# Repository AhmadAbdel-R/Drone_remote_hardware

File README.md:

# Drone Remote Hardware

Hardware workspace for my capstone remote + FCU board iterations.

## Repo Layout

- `hardware/fcu/FCU-hardware/`
  - FCU KiCad project and production artifacts
- `hardware/remote/FC_Remote-hardware/`
  - remote controller KiCad project and production artifacts
- `hardware/remote/FC_Remote-hardware/nrf_breakout/`
  - nRF breakout board subproject
- `mechanical/enclosure/`
  - enclosure and mechanical exports
- `mechanical/enclosure/remote_enclosure_stl/`
  - upload area for new remote enclosure STL revisions
- `mechanical/fcu/top_plate_updated_frame/`
  - upload area for updated FCU top plate/frame files
- `docs/`
  - repo organization notes

## Tools

- KiCad for schematic + PCB
- STEP/STL/3MF for mechanical handoff

## Practical Note

A lot of old backups and generated production files are intentionally kept for traceability between board revisions.

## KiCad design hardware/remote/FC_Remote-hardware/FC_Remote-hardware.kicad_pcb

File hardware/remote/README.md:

# Remote Hardware

This folder contains the primary remote controller PCB project.

Main KiCad project path:

- `FC_Remote-hardware.kicad_pro`

Also includes:

- manufacturing outputs
- historical backups
- support subprojects (including nRF breakout)

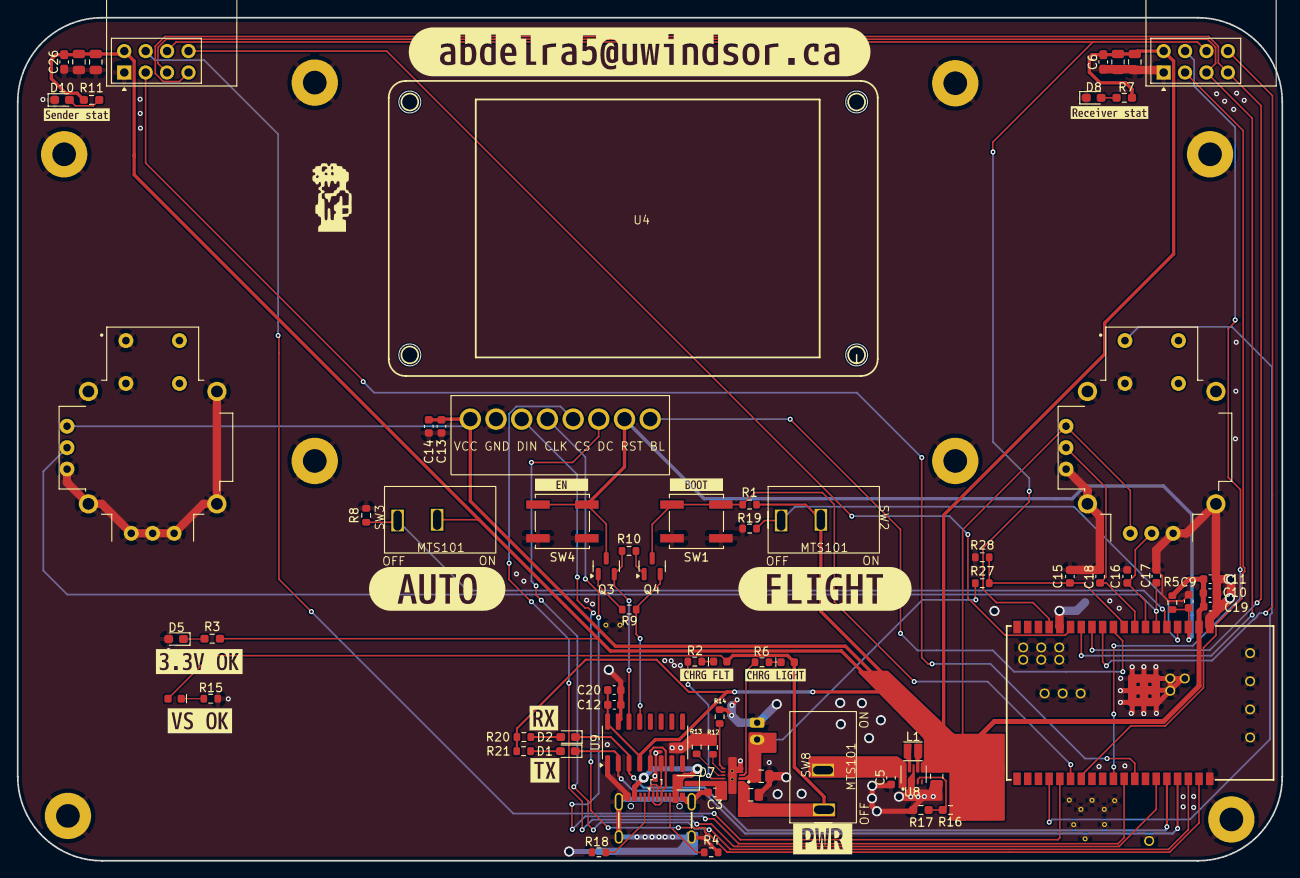
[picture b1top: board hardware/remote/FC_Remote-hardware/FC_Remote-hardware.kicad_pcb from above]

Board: 4 copper layers, 150.0 x 100.0 mm, 89 parts (1 on the bottom side), 56 nets.

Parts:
BT1: Battery_Cell; JST_PH_B2B-PH-K_1x02_P2.00mm_Vertical
C1, C2, C4, C7, C8, C21, C22: 22uF; C_0805_2012Metric
C3, C9, C10, C12, C13: 1uF; C_0603_1608Metric
C5, C11: 10uF; C_0603_1608Metric
C6, C26: 0.1uF; C_0603_1608Metric_Pad1.08x0.95mm_HandSolder
C14, C15, C16, C17, C18, C19, C20: 0.1uF; C_0603_1608Metric
D1, D2, D5: LED; LED_0603_1608Metric_Pad1.05x0.95mm_HandSolder
D3: Green; LED_0603_1608Metric_Green
D4: Yellow; LED_0603_1608Metric_Yellow
D6: Red; LED_0603_1608Metric_Red
D7: PMEG4020EJ; D_SOD-323
D8, D10: GREEN; LED_0603_1608Metric_Pad1.05x0.95mm_HandSolder
J1: USB_C_Receptacle; USB-C_16
L1: 0.47 uH; L_Changjiang_FTC201608S
Q3, Q4: MMBT2222A; SOT-23
R1, R5: 10k; R_0603_1608Metric
R2, R6: 5K; R_0603_1608Metric
R3, R7, R11: 5K; R_0603_1608Metric_Pad0.98x0.95mm_HandSolder
R4, R18: 5.1k; R_0603_1608Metric
R8, R9, R10, R14, R19, R27, R28: 10K; R_0603_1608Metric
R12: 13K; R_0603_1608Metric
R13: 600; R_0603_1608Metric
R15: 1K; R_0603_1608Metric
R16: 511K; R_0603_1608Metric_Pad0.98x0.95mm_HandSolder
R17: 91K; R_0603_1608Metric_Pad0.98x0.95mm_HandSolder
R20, R21: 470; R_0603_1608Metric
SW1, SW4: SW_Push; SW_Push_1P1T_NO_CK_KSC7xxJ
SW2, SW3, SW8: SW_SPST; mts101sw
U1, U2: COM-09032; XDCR_COM-09032
U3: BQ25185DLHR; IC_BQ25185DLHR
U4: ST7789_2IN_WS; Waveshare_2inch_foot
U5: ESP32-WROVER-E-N16R8; ESP32-WROVER-E-IE
U6: TPD2EUSB30; Texas_DRT-3
U7, U12: NRF24L01_Breakout; nRF24L01_Breakout
U8: TPS63802DLAR; VREG_TPS63802DLAR
U9: CH340C; SOIC-16_3.9x9.9mm_P1.27mm
kibuzzard-69B816EF: G***; kibuzzard-69B816EF
kibuzzard-69B818B8: G***; kibuzzard-69B818B8
kibuzzard-69B818DE: G***; kibuzzard-69B818DE
kibuzzard-69B825AF: G***; kibuzzard-69B825AF
kibuzzard-69B825F7: G***; kibuzzard-69B825F7
kibuzzard-69B842D9: G***; kibuzzard-69B842D9
kibuzzard-69B842E6: G***; kibuzzard-69B842E6
kibuzzard-69B8345C: G***; kibuzzard-69B8345C
kibuzzard-69B8399F: G***; kibuzzard-69B8399F
kibuzzard-69B81705: G***; kibuzzard-69B81705
kibuzzard-69B83530: G***; kibuzzard-69B83530
kibuzzard-69B84485: G***; kibuzzard-69B84485
kibuzzard-69B84493: G***; kibuzzard-69B84493
kibuzzard-6967276B: G***; kibuzzard-6967276B

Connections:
0_ESP: Q4.3 (C), R1.1, SW1.1, U5.25 (IOA0)
+3.3V: C1.1, C6.1, C7.1, C8.1, C10.1, C11.2, C12.2, C13.1, C14.1, C19.2, C20.2, C21.1, C22.1, C26.1, R1.2, R3.2, R5.1, R7.1, R11.1, R16.1, R20.1, R21.1, SW2.2 (B), SW3.2 (B), U1.V1 (V+), U2.H1 (H+), U2.V1 (V+), U4.1 (VCC), U5.2 (VDD), U7.2 (VCC), U8.6 (VOUT), U9.4 (V3), U9.16 (VCC), U12.2 (VCC)
+5V: C3.1, D7.1 (K), U3.10 (IN)
AUTONOMY_SW: R8.1, SW3.1 (A), U5.5 (IA39)
BATT_ADC: C15.1, R27.2, R28.2, U5.9 (IOA33)
CHIP_PU: C9.1, Q3.3 (C), R5.2, SW4.1, U4.7 (RST), U5.3 (EN)
CTRL_CE: U5.31 (IO19), U12.3 (CE)
CTRL_CSN: U5.24 (IOA2), U12.4 (~CSN)
CTRL_IRQ: U5.14 (IOA12), U12.8 (IRQ)
DIR_JOY_BTN: U2.B1A (SEL+), U5.23 (IOA15)
DIR_JOY_X: C16.1, U2.H2 (H), U5.7 (IA35)
DIR_JOY_Y: C18.1, U2.V2 (V), U5.8 (IOA32)
DTR: Q4.2 (E), R9.2, U9.13 (~DTR)
FLIGHT_MODE_SW: R19.1, SW2.1 (A), U5.4 (IA36)
GND: BT1.1 (+), C1.2, C2.2, C3.2, C4.2, C5.2, C6.2, C7.2, C8.2, C9.2, C10.2, C11.1, C12.1, C13.2, C14.2, C15.2, C16.2, C17.2, C18.2, C19.1, C20.1, C21.2, C22.2, C26.2, D5.2 (A), D8.1 (K), D10.1 (K), J1.GND, J1.NC1, J1.NC2, J1.NC3, J1.S (NC), R4.2, R8.2, R12.1, R13.1, R14.2, R15.1, R17.2, R18.2, R19.2, R28.1, SW1.2, SW4.2, U1.B1A (SEL+), U1.B2A (SEL-), U1.H1 (H+), U1.H2 (H), U1.H3 (H-), U1.S1 (SHIELD), U1.S2 (SHIELD), U1.S3 (SHIELD), U1.S4 (SHIELD), U1.V3 (V-), U2.B2A (SEL-), U2.H3 (H-), U2.S1 (SHIELD), U2.S2 (SHIELD), U2.S3 (SHIELD), U2.S4 (SHIELD), U2.V3 (V-), U3.4 (~CE), U3.5 (GND), U3.11 (THERMAL_PAD), U3.12, U3.13, U4.2 (GND), U5.1 (GND), U5.15 (GND), U5.38 (GND), U5.39.1 (GND), U5.39.2 (GND), U5.39.3 (GND), U5.39.4 (GND), U5.39.5 (GND), U5.39.6 (GND), U5.39.7 (GND), U5.39.8 (GND), U5.39.9 (GND), U6.3 (GND), U7.1 (GND), U8.2 (MODE), U8.3 (AGND), U8.8 (GND), U9.1 (GND), U9.15 (R232), U12.1 (GND)
NRF_MISO: U5.12 (IOA27), U7.7 (MISO), U12.7 (MISO)
NRF_MOSI: U5.16 (IOA13), U7.6 (MOSI), U12.6 (MOSI)
NRF_SCK: U5.13 (IOA14), U7.5 (SCK), U12.5 (SCK)
unnamed: D1.2 (A), R21.2
unnamed: D2.2 (A), R20.2
unnamed: D3.1 (K), R15.2
unnamed: D4.1 (K), R6.1
unnamed: D5.1 (K), R3.1
unnamed: D6.1 (K), R2.1
unnamed: D7.2 (A), J1.VBUS
unnamed: D8.2 (A), R7.2
unnamed: D10.2 (A), R11.2
unnamed: J1.A5 (CC1), R18.1
unnamed: J1.B5 (CC2), R4.1
unnamed: Q3.1 (B), R9.1
unnamed: Q4.1 (B), R10.2
unnamed: R12.2, U3.7 (ILIM/VSET)
unnamed: R13.2, U3.8 (ISET)
unnamed: R2.2, U3.9 (STAT1)
unnamed: R6.2, U3.3 (STAT2)
unnamed: R14.1, U3.6 (TS/MR)
unnamed: R16.2, R17.1, U8.4 (FB)
unnamed: L1.2, U8.9 (L1)
unnamed: L1.1, U8.7 (L2)
RTS: Q3.2 (E), R10.1, U9.14 (~RTS)
RX_ESP: D2.1 (K), U5.34 (RXD0/IO3), U9.3 (RXD)
TELM_CE: U5.26 (IOA4), U7.3 (CE)
TELM_CSN: U5.29 (IO5), U7.4 (~CSN)
TELM_IRQ: U5.11 (IOA26), U7.8 (IRQ)
TFT_BL: U4.8 (BL), U5.10 (IOA25)
TFT_CS: U4.5 (CS), U5.33 (IO21)
TFT_DC: U4.6 (DC), U5.36 (IO22)
TFT_MOSI: U4.3 (DIN), U5.37 (IO23)
TFT_SCK: U4.4 (SCLK), U5.30 (IO18)
THROTTLE_JOY: C17.1, U1.V2 (V), U5.6 (IA34)
TX_ESP: D1.1 (K), U5.35 (TXD0/IO1), U9.2 (TXD)
USB_D+_ESP: J1.A6 (D+), J1.B6 (D+), U6.1 (D+), U9.5 (UD+)
USB__D-_ESP: J1.A7 (D-), J1.B7 (D-), U6.2 (D-), U9.6 (UD-)
VBAT: BT1.2 (-), C4.1, R27.1, U3.2 (BAT)
VIN_3.3: C5.1, SW8.2 (B), U8.1 (EN), U8.10 (VIN)
VS: C2.1, D3.2 (A), D4.2 (A), D6.2 (A), SW8.1 (A), U3.1 (SYS)

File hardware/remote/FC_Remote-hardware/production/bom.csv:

Designator,Footprint,Quantity,Value,LCSC Part #
BT1,JST_PH_B2B-PH-K_1x02_P2.00mm_Vertical,1,Battery_Cell,
"C1, C2, C21, C22, C4, C7, C8",0805,7,22uF,
"C10, C12, C13, C3, C9",0603,5,1uF,
"C11, C5",0603,2,10uF,
"C14, C15, C16, C17, C18, C19, C20, C26, C6",0603,9,0.1uF,
"D1, D2, D5",0603,3,LED,
"D10, D3, D8",0603,3,GREEN,
D4,0603,1,Yellow,
D6,0603,1,Red,
D7,D_SOD-323,1,PMEG4020EJ,
J1,USB-C_16,1,USB_C_Receptacle,
L1,L_Changjiang_FTC201608S,1,0.47 uH,
"Q3, Q4",SOT-23,2,MMBT2222A,
"R1, R10, R14, R19, R27, R28, R5, R8, R9",0603,9,10k,
"R11, R2, R3, R6, R7",0603,5,5K,
R12,0603,1,13K,
R13,0603,1,600,
R15,0603,1,1K,
R16,0603,1,511K,
R17,0603,1,91K,
"R18, R4",0603,2,5.1k,
"R20, R21",0603,2,470,
"SW1, SW4",SW_Push_1P1T_NO_CK_KSC7xxJ,2,SW_Push,
"SW2, SW3, SW8",mts101sw,3,SW_SPST,
"U1, U2",XDCR_COM-09032,2,COM-09032,
"U12, U7",nRF24L01_Breakout,2,NRF24L01_Breakout,
U3,IC_BQ25185DLHR,1,BQ25185DLHR,
U4,Waveshare_2inch_foot,1,ST7789_2IN_WS,
U5,ESP32-WROVER-E-IE,1,ESP32-WROVER-E-N16R8,
U6,Texas_DRT-3,1,TPD2EUSB30,
U8,VREG_TPS63802DLAR,1,TPS63802DLAR,
U9,SOIC-16_3.9x9.9mm_P1.27mm,1,CH340C,

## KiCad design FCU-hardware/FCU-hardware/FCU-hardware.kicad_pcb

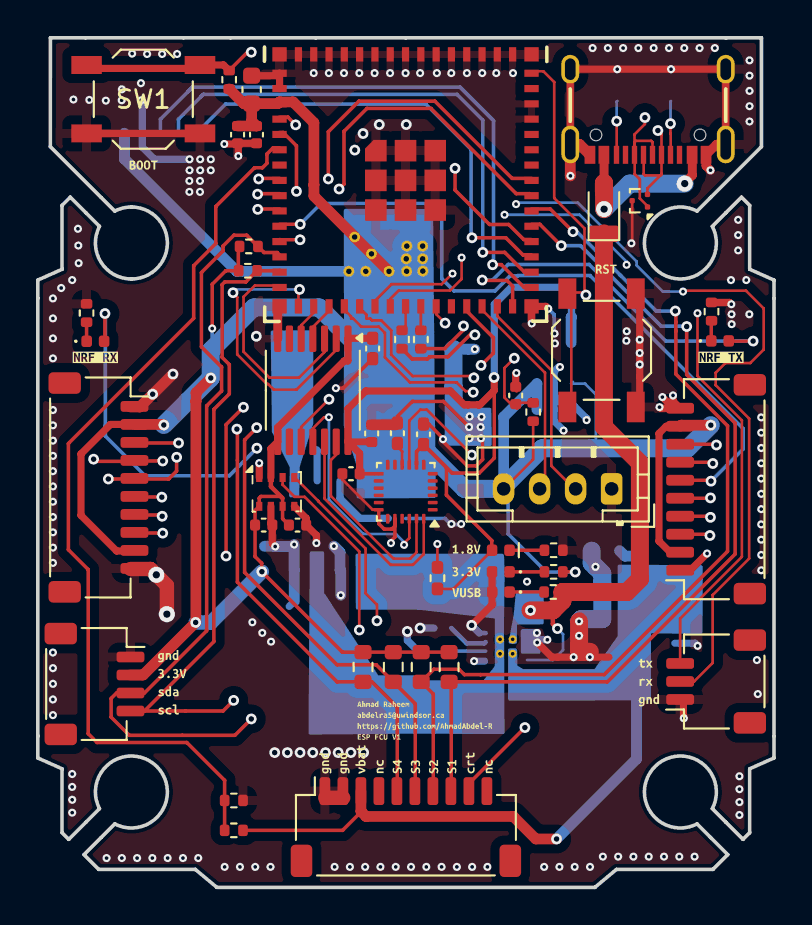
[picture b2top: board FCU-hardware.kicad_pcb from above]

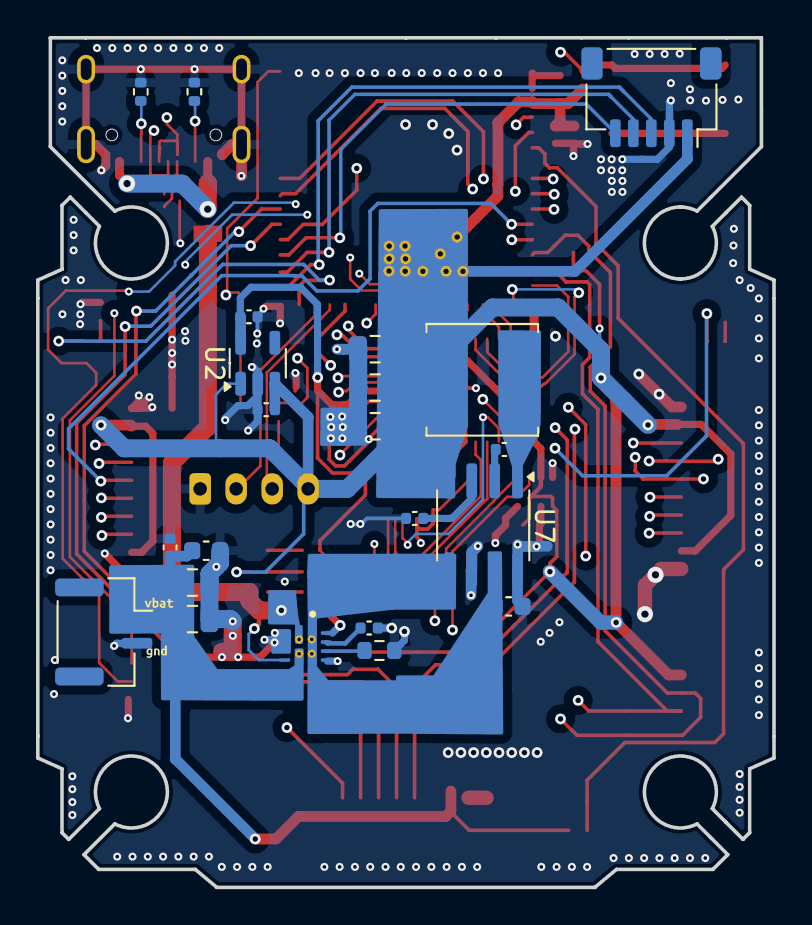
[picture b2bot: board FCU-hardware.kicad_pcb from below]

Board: 4 copper layers, 40.9 x 47.2 mm, 84 parts (24 on the bottom side), 60 nets.

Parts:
C1, C13, C15, C17, C19, C20, C23: 0.1uF; C_0402_1005Metric
C2, C3, C9, C10, C16, C18: 1uF; C_0402_1005Metric
C4, C12, C14: 0.1uF; C_0402_1005Metric_Pad0.74x0.62mm_HandSolder
C5, C6, C7, C21, C22: 22uF; C_0805_2012Metric
C8, C11: 10uF; C_0603_1608Metric
C24: 1uF; C_0603_1608Metric
D1: Red; LED_0402_1005Metric_Red
D2: Blue; LED_0402_1005Metric
D3, D4: Green; LED_0402_1005Metric
D5: LED; LED_0402_1005Metric
D7: PMEG4020EJ; D_SOD-323
J1: USB_C_Receptacle; USB-C_16(CUSTOM)
J2: Conn_01x04; JST_SH_SM04B-SRSS-TB_1x04-1MP_P1.00mm_Horizontal
J4: Conn_01x04; JST_PH_B4B-PH-K_1x04_P2.00mm_Vertical
J5: Conn_01x03; JST_SH_SM03B-SRSS-TB_1x03-1MP_P1.00mm_Horizontal
J7, J8, J15: Conn_01x10; JST_SH_SM10B-SRSS-TB_1x10-1MP_P1.00mm_Horizontal
J9: Conn_01x02; JST_GH_SM02B-GHS-TB_1x02-1MP_P1.25mm_Horizontal
J14: Conn_01x05; JST_SH_SM05B-SRSS-TB_1x05-1MP_P1.00mm_Horizontal
L1: 22 uH; L_Bourns_SRN6045TA
R1, R2: 22; R_0402_1005Metric
R3: 1.5K; R_0402_1005Metric
R4, R18: 5.1k; R_0402_1005Metric
R5, R6: 10k; R_0402_1005Metric
R7: 59K; R_0603_1608Metric
R8: 500; R_0402_1005Metric
R9, R10: 4.7K; R_0402_1005Metric
R11: 3K; R_0402_1005Metric
R12, R13: 1K; R_0402_1005Metric
R14: 22K; R_0402_1005Metric
R15: 100K; R_0402_1005Metric
R19: 100K; R_0402_1005Metric_Pad0.72x0.64mm_HandSolder
R28, R29, R30, R31: DNP; R_0603_1608Metric
SW1, SW4: SW_Push; SW_SPST_TL3342
U1: ESP32-S3-MINI; ESP32-MINI
U2: MIC5504-1.8YM5-TR; SOT-23-5
U3: ICM-20948; InvenSense_QFN-24_3x3mm_P0.4mm
U4: TXU0304PWR; TSSOP-14_4.4x5mm_P0.65mm
U5: BMP280; Bosch_LGA-8_2x2.5mm_P0.65mm_ClockwisePinNumbering
U6: TPD2EUSB30; Texas_DRT-3
U7: L6982N33DR; SOIC-8_3.9x4.9mm_P1.27mm
U8: TPS2121RUXR; IC_TPS2121RUXR
kibuzzard-69CA970F: G***; kibuzzard-69CA970F
kibuzzard-69CA973C: G***; kibuzzard-69CA973C
kibuzzard-69CA975F: G***; kibuzzard-69CA975F
kibuzzard-69CA983A: G***; kibuzzard-69CA983A
kibuzzard-69CA985D: G***; kibuzzard-69CA985D
kibuzzard-69CA986D: G***; kibuzzard-69CA986D
kibuzzard-69CA9883: G***; kibuzzard-69CA9883
kibuzzard-69CAA37E: G***; kibuzzard-69CAA37E
kibuzzard-69CAA38B: G***; kibuzzard-69CAA38B
kibuzzard-69CAA374: G***; kibuzzard-69CAA374
kibuzzard-69CD68AD: G***; kibuzzard-69CD68AD
kibuzzard-69CD68C1: G***; kibuzzard-69CD68C1
kibuzzard-69CDB16D: G***; kibuzzard-69CDB16D

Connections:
0_ESP: R6.1, SW1.1, U1.4 (IO0)
1.8V: C3.2, C12.2, C13.1, C15.2, D1.2 (A), R19.2, U2.5 (VOUT), U3.8 (VDDIO), U3.13 (VDD), U4.14 (VCCB)
+3.3V: C2.2, C5.1, C10.1, C11.2, C14.1, C16.2, C17.1, C19.2, C21.1, C22.1, J2.2, J4.4, J7.2, J7.9, J14.1, J15.2, J15.9, L1.2, R3.2, R5.1, R6.2, R9.1, R10.1, R28.1, R29.1, R30.1, R31.1, U1.3 (3V3), U2.1 (VIN), U2.3 (EN), U4.1 (VCCA), U4.8 (OE), U5.2 (CSB), U5.6 (VDDIO), U5.8 (VDD), U7.4 (VOUT/FB)
CHIP_PU: C9.1, R5.2, SW4.1, U1.45 (EN)
CRT: J8.9, U1.5 (IOA1)
CS/1.8: R19.1, U3.22 (~CS), U4.11 (B3Y)
CTRL_CE: J15.7, U1.19 (IOA15)
CTRL_CSN: J15.6, U1.11 (IOA7)
CTRL_IRQ: J15.8, U1.20 (IOA16)
D+: J1.A6 (D+), J1.B6 (D+), R1.2, U6.1 (D+)
D-: J1.A7 (D-), J1.B7 (D-), R2.2, U6.2 (D-)
GND: C2.1, C3.1, C4.2, C5.2, C6.2, C7.2, C8.1, C9.2, C10.2, C11.1, C12.1, C13.2, C14.2, C15.1, C16.1, C17.2, C18.2, C19.1, C20.2, C21.2, C22.2, C23.1, C24.2, D2.2 (A), D5.2 (A), J1.GND, J1.S (SHIELD), J2.1, J4.1, J5.1, J7.1, J7.10, J8.1, J8.2, J9.2, J14.2, J15.1, J15.10, R4.2, R7.2, R8.2, R12.2, R13.2, R14.2, R18.2, SW1.2, SW4.2, U1.1 (GND), U1.2 (GND), U1.42 (GND), U1.43 (GND), U1.46 (GND), U1.47 (GND), U1.48 (GND), U1.49 (GND), U1.50 (GND), U1.51 (GND), U1.52 (GND), U1.53 (GND), U1.54 (GND), U1.55 (GND), U1.56 (GND), U1.57 (GND), U1.58 (GND), U1.59 (GND), U1.60 (GND), U1.61 (GND), U1.62 (GND), U1.63 (GND), U1.64 (GND), U1.65 (GND), U2.2 (GND), U3.18 (GND), U3.20 (GND), U4.7 (GND), U5.1 (GND), U5.5 (SDO), U5.7 (GND), U6.3 (GND), U7.6 (AGND), U7.8 (PGND), U8.3 (CP2), U8.4 (OV2), U8.5 (OV1), U8.9 (ST), U8.12 (GND)
IMU_CS: U1.18 (IOA14), U4.4 (A3)
IO35: J14.3, U1.31 (IO35)
IO36: J14.4, U1.32 (IO36)
IO37: J14.5, U1.33 (IO37)
MOTOR1: J8.8, R28.2, U1.35 (IO39)
MOTOR2: J8.7, R29.2, U1.36 (IO40)
MOTOR3: J8.6, R30.2, U1.37 (IO41)
MOTOR4: J8.5, R31.2, U1.38 (IO42)
NRFRX_OK: D4.2 (A), U1.27 (IO47)
NRFTX_OK: D3.2 (A), U1.30 (IO48)
NRF_MISO: J7.5, J15.5, U1.9 (IOA5)
NRF_MOSI: J7.4, J15.4, U1.8 (IOA4)
NRF_SCK: J7.3, J15.3, U1.10 (IOA6)
unnamed: D1.1 (K), R8.1
unnamed: D2.1 (K), R11.1
unnamed: D3.1 (K), R12.1
unnamed: D4.1 (K), R13.1
unnamed: D5.1 (K), R3.1
unnamed: D7.2 (A), J1.VBUS
unnamed: J1.A5 (CC1), R18.1
unnamed: J1.B5 (CC2), R4.1
unnamed: R2.1, U1.23 (IOA19)
unnamed: R1.1, U1.24 (IOA20)
unnamed: C4.1, U3.10 (REGOUT)
unnamed: C1.1, U7.2 (BOOT)
unnamed: C1.2, L1.1, U7.1 (SW)
unnamed: C18.1, U7.3 (VCC)
unnamed: R7.1, U8.10 (ILIM)
unnamed: C23.2, U8.11 (SS)
RX_GPS: J4.2, U1.29 (IO34)
RX_RASBERRY: J5.2, U1.22 (IOA18)
SCK_IMU: U1.16 (IOA12), U4.2 (A1)
SCK/1.8V: U3.23 (SCL/SCLK), U4.13 (B1Y)
SCL: J2.4, R10.2, U1.14 (IOA10), U5.4 (SCK)
SDA: J2.3, R9.2, U1.13 (IOA9), U5.3 (SDI)
SDI_IMU: U1.15 (IOA11), U4.3 (A2)
SDI/1.8V: U3.24 (SDA/SDI), U4.12 (B2Y)
SDO_IMU: U1.17 (IOA13), U4.5 (A4Y)
SDO/1.8V: U3.9 (SDO/AD0), U4.10 (B4)
TELM_CE: J7.7, U1.25 (IO21)
TELM_CSN: J7.6, U1.12 (IOA8)
TELM_IRQ: J7.8, U1.34 (IO38)
TX_GPS: J4.3, U1.28 (IO33)
TX_RASBERRY: J5.3, U1.21 (IOA17)
VBAT: C6.1, C7.1, C20.1, C24.1, J8.3, J9.1, R15.1, U8.7 (IN1), U8.7_1 (IN1__1)
VBAT_ADC: R14.1, R15.2, U1.6 (IOA2)
VBUS: D7.1 (K), R11.2, U8.2 (IN2), U8.2_1 (IN2__1), U8.6 (PR1)
VIN_3.3: C8.2, U7.5 (EN/CLKIN), U7.7 (VIN), U8.1 (OUT), U8.1_1 (OUT__1), U8.8 (OUT__2), U8.8_1 (OUT__3)

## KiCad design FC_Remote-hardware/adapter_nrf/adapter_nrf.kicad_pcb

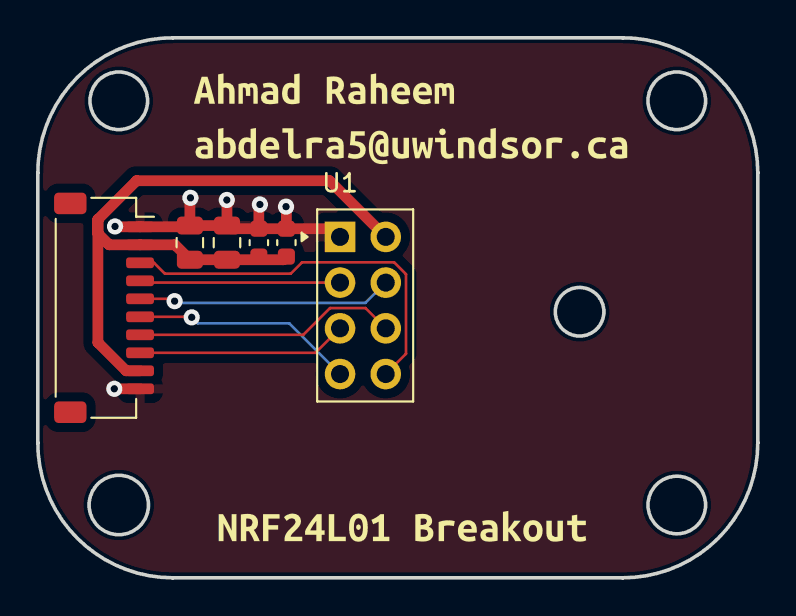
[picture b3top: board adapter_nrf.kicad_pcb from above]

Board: 4 copper layers, 40.0 x 30.0 mm, 8 parts (0 on the bottom side), 8 nets.

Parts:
C1, C2: 22uF; C_0805_2012Metric
C3: 0.1uF; C_0603_1608Metric
C4: 1.0uF; C_0603_1608Metric
J1: Conn_01x10; JST_SH_SM10B-SRSS-TB_1x10-1MP_P1.00mm_Horizontal
U1: NRF24L01_Breakout; nRF24L01_Breakout
kibuzzard-69CDF508: G***; kibuzzard-69CDF508
kibuzzard-69CDF522: G***; kibuzzard-69CDF522

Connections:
3.3V: C1.1, C2.1, C3.1, C4.1, J1.2, J1.9, U1.2 (VCC)
CE: J1.4, U1.3 (CE)
CSN: J1.5, U1.4 (~CSN)
GND: C1.2, C2.2, C3.2, C4.2, J1.1, J1.10, U1.1 (GND)
IRQ: J1.3, U1.8 (IRQ)
MISO: J1.6, U1.7 (MISO)
MOSI: J1.7, U1.6 (MOSI)
SCK: J1.8, U1.5 (SCK)

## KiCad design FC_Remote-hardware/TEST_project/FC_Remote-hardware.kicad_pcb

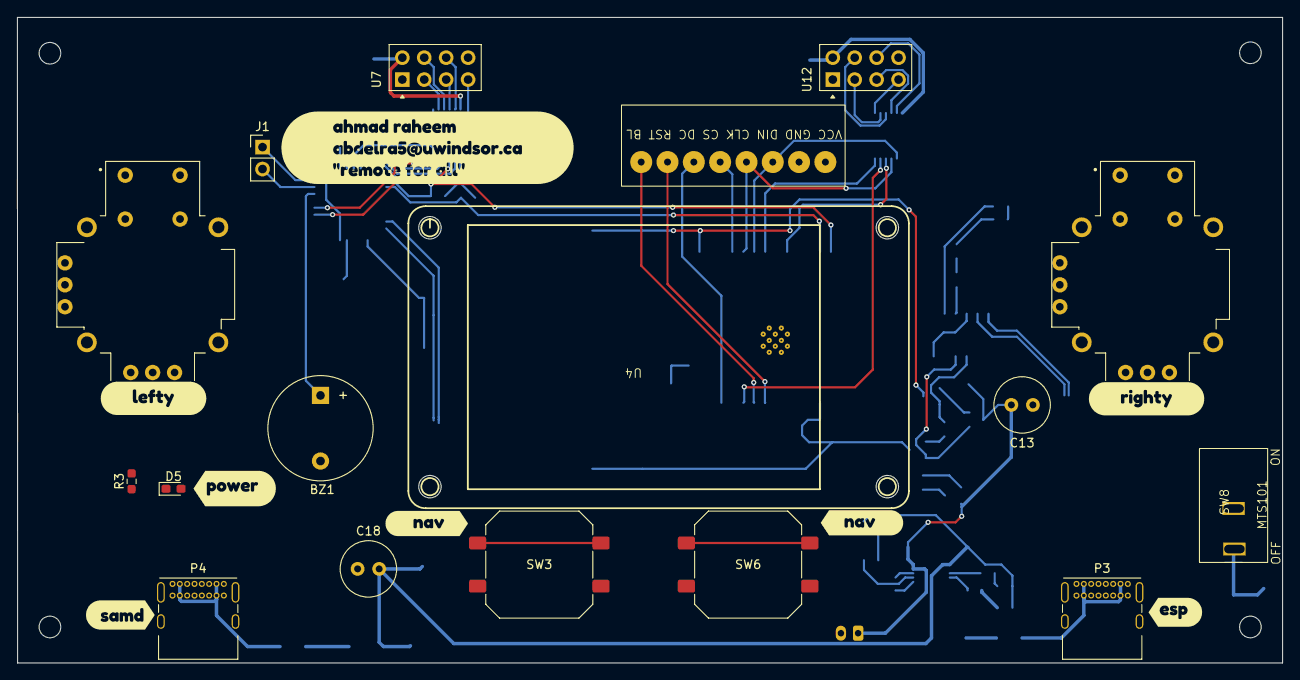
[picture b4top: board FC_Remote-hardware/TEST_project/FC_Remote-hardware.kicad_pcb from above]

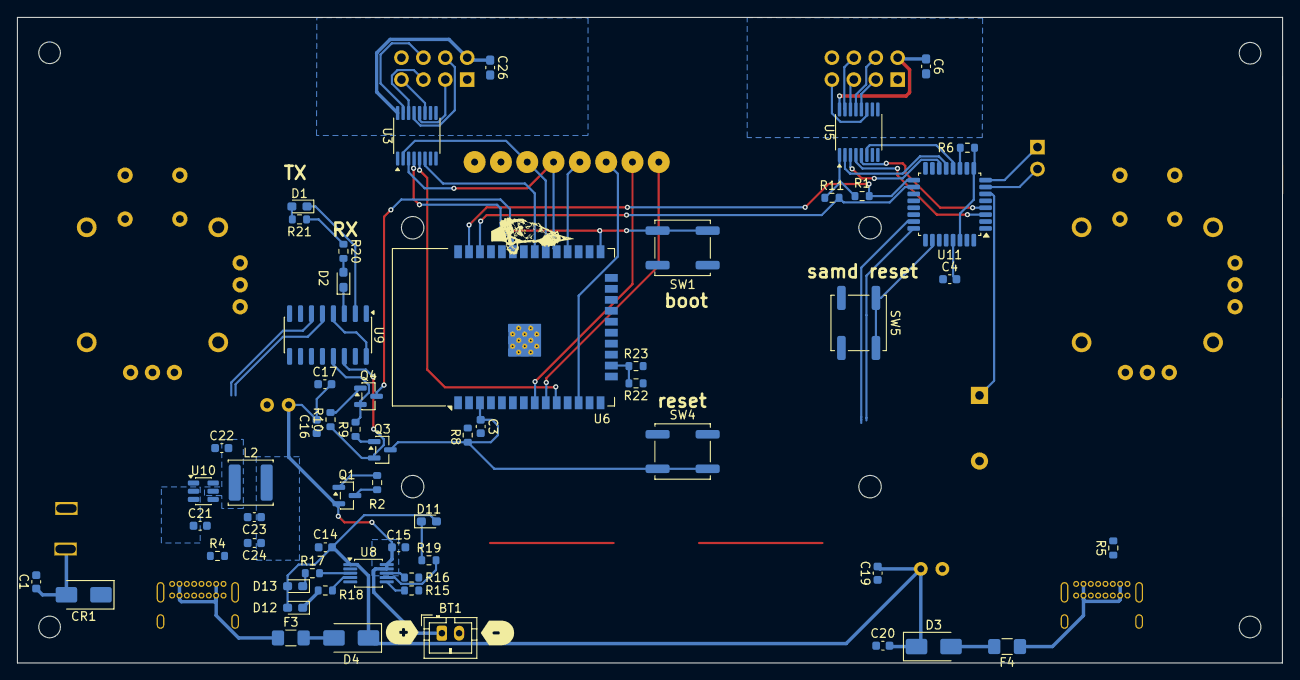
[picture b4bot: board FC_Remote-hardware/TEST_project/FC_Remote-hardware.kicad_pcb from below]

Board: 4 copper layers, 146.6 x 74.8 mm, 84 parts (60 on the bottom side), 81 nets.

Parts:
BT1: Battery_Cell; JST_PH_B2B-PH-K_1x02_P2.00mm_Vertical
BZ1: Buzzer; Buzzer_12x9.5RM7.6
C1, C16, C19, C21: 10uF; C_0603_1608Metric
C3, C4, C14, C15: 1uF; C_0603_1608Metric
C6, C26: 0.1uF; C_0603_1608Metric_Pad1.08x0.95mm_HandSolder
C13, C18: 100uF; C_Radial_D6.3mm_H5.0mm_P2.50mm
C17, C20: 0.1uF; C_0603_1608Metric
C22: 100 nF; C_0603_1608Metric
C23, C24: 22uF; C_0603_1608Metric
CR1: SSA210; D_SMA
D1, D2, D5, D11, D12, D13: LED; LED_0603_1608Metric_Pad1.05x0.95mm_HandSolder
D3, D4: SMAJ5.0A; D_SMA
F3, F4: Polyfuse; Fuse_1206_3216Metric_Pad1.42x1.75mm_HandSolder
J1: Conn_01x02_Pin; PinHeader_1x02_P2.54mm_Vertical
L2: 3.9uH; L_APV_ANR5020
P3, P4: USB_C_Plug_USB2.0; USB_C_Receptacle_GCT_USB4085
Q1: DMG3415U; SOT-23
Q3, Q4: MMBT2222A; SOT-23
R1, R11: DNP; R_0603_1608Metric
R2, R22, R23: 100K; R_0603_1608Metric
R3: 500; R_0603_1608Metric_Pad0.98x0.95mm_HandSolder
R4, R5: 5.1k; R_0603_1608Metric
R6: 5.1K; R_0603_1608Metric
R8: 10k; R_0603_1608Metric
R9, R10, R16: 10K; R_0603_1608Metric
R15: 1K; R_0603_1608Metric
R17, R18, R19: 470; R_0603_1608Metric
R20, R21: R; R_0603_1608Metric
SW1, SW4, SW5: SW_Push; SW_Push_1P1T_NO_CK_KSC7xxJ
SW3, SW6: SW_Push; SW_Push_1P1T_NO_CK_PTS125Sx85SMTR
SW8: SW_SPST; mts101sw
U1, U2: COM-09032; XDCR_COM-09032
U3, U5: Si8662BB-AU; QSOP-16_3.9x4.9mm_P0.635mm
U4: ST7789_2IN_WS; Waveshare_2inch_foot
U6: ESP32-WROOM-32D
U7, U12: NRF24L01_Breakout; nRF24L01_Breakout
U8: MCP73833-xxx-UN; MSOP-10_3x3mm_P0.5mm
U9: CH340C; SOIC-16_3.9x9.9mm_P1.27mm
U10: AP63203WU; TSOT-23-6
U11: ATSAMD21E16A-A; TQFP-32_7x7mm_P0.8mm
kibuzzard-69148B4C: G***; kibuzzard-69148B4C
kibuzzard-69148B5C: G***; kibuzzard-69148B5C
kibuzzard-69148BBB: G***; kibuzzard-69148BBB
kibuzzard-69148BF6: G***; kibuzzard-69148BF6
kibuzzard-69173B40: G***; kibuzzard-69173B40
kibuzzard-69173BBC: G***; kibuzzard-69173BBC
kibuzzard-69173C5C: G***; kibuzzard-69173C5C
kibuzzard-69173C8F: G***; kibuzzard-69173C8F
kibuzzard-691487BB: G***; kibuzzard-691487BB
kibuzzard-6914879A: G***; kibuzzard-6914879A

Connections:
0_ESP: Q4.3 (C), SW1.1, U6.25 (IO0)
13_ESP: R22.2, R23.1, U6.16 (IO13)
14_ESP: U2.H2 (H), U6.13 (IO14)
15_ESP: SW3.1, U6.23 (IO15)
16_ESP: SW6.1, U6.27 (IO16)
17_ESP: U4.5 (CS), U6.28 (IO17)
21_ESP: U3.4 (A3), U6.33 (IO21)
27_ESP: U4.6 (DC), U6.12 (IO27)
32_ESP: U4.7 (RST), U6.8 (IO32)
33_ESP: U4.8 (BL), U6.9 (IO33)
+3.3V: C23.1, C24.1, L2.2, R1.1, R3.2, R6.2, R8.1, R11.1, R20.1, R21.1, U1.H1 (H+), U1.V1 (V+), U2.H1 (H+), U2.V1 (V+), U3.1 (VDD1), U4.1 (VCC), U5.1 (VDD1), U6.2 (VDD), U9.4 (V3), U9.16 (VCC), U10.1 (FB), U11.9 (VDDANA), U11.30 (VDDIN)
+3.3V_nrf1: C26.1, U3.16 (VDD2), U12.2 (VCC)
+3.3V_nrf2: C6.1, U5.16 (VDD2), U7.2 (VCC)
+5V: C14.1, C18.2, C19.2, C20.2, CR1.1, D3.1 (A1), D4.1 (A1), D11.2 (A), D12.2 (A), D13.2 (A), U8.1 (V_{DD}), U8.2 (V_{DD})
/power/sw: C22.2, L2.1, U10.5 (SW)
A1_ESP: U3.5 (A4), U6.10 (IO25)
A5_ESP: U2.V2 (V), U6.26 (IO4)
CHIP_PU: C3.1, Q3.3 (C), R8.2, SW4.1, U6.3 (EN)
DTR: Q4.2 (E), R9.2, U9.13 (~DTR)
GND: BT1.2 (-), BZ1.2 (-), C1.2, C3.2, C4.1, C13.1, C14.2, C15.2, C16.1, C17.1, C18.1, C19.1, C20.1, C21.2, C23.2, C24.2, D5.2 (A), P3.A1 (GND), P3.A12 (GND), P3.B1 (GND), P3.B12 (GND), P3.S1 (SHIELD), P4.A1 (GND), P4.A12 (GND), P4.B1 (GND), P4.B12 (GND), P4.S1 (SHIELD), R4.2, R5.2, R15.2, R16.2, R23.2, SW1.2, SW3.2, SW4.2, SW5.1, SW6.2, U1.B2A (SEL-), U1.H3 (H-), U1.S1 (SHIELD), U1.S2 (SHIELD), U1.S3 (SHIELD), U1.S4 (SHIELD), U1.V3 (V-), U2.B2A (SEL-), U2.H3 (H-), U2.S1 (SHIELD), U2.S2 (SHIELD), U2.S3 (SHIELD), U2.S4 (SHIELD), U2.V3 (V-), U3.8 (GND1), U4.2 (GND), U5.8 (GND1), U6.1 (GND), U6.15 (GND), U6.38 (GND), U6.39 (GND), U8.5 (V_{SS}), U9.1 (GND), U10.4 (GND), U11.10 (GND), U11.28 (GND)
GND_nrf1: C26.2, U3.9 (GND2), U12.1 (GND)
GND_nrf2: C6.2, U5.9 (GND2), U7.1 (GND)
I34_ESP: U1.H2 (H), U6.6 (IO34)
I35_ESP: U1.V2 (V), U6.7 (IO35)
MISO_ESP: U3.6 (A5), U6.31 (IO19)
MOSI_ESP: U3.2 (A1), U4.3 (DIN), U6.30 (IO18)
unnamed: D1.2 (A), R21.2
unnamed: D2.2 (A), R20.2
unnamed: D3.2 (A2), F4.2
unnamed: D4.2 (A2), F3.2
unnamed: D5.1 (K), R3.1
unnamed: D11.1 (K), R19.1
unnamed: D12.1 (K), R18.1
unnamed: D13.1 (K), R17.1
unnamed: F3.1, P3.A4 (VBUS), P3.A9 (VBUS), P3.B4 (VBUS), P3.B9 (VBUS)
unnamed: F4.1, P4.A4 (VBUS), P4.A9 (VBUS), P4.B4 (VBUS), P4.B9 (VBUS)
unnamed: P3.A5 (CC), R4.1
unnamed: P4.A5 (CC), R5.1
unnamed: Q1.1 (G), R2.2
unnamed: Q3.1 (B), R9.1
unnamed: Q4.1 (B), R10.2
unnamed: U5.15 (B1), U7.6 (MOSI)
unnamed: U5.14 (B2), U7.5 (SCK)
unnamed: U5.13 (B3), U7.4 (~CSN)
unnamed: U5.12 (B4), U7.3 (CE)
unnamed: U5.11 (B5), U7.7 (MISO)
unnamed: R15.1, U8.6 (PROG)
unnamed: R17.2, U8.3 (STAT1)
unnamed: R18.2, U8.4 (STAT2)
unnamed: R16.1, U8.8 (THERM)
unnamed: R19.2, U8.7 (~PG)
unnamed: C22.1, U10.6 (BST)
unnamed: C4.2, U11.29 (VDDCORE)
unnamed: SW5.2, U11.26 (~RESET)
unnamed: U3.12 (B4), U12.3 (CE)
unnamed: U3.11 (B5), U12.7 (MISO)
unnamed: U3.15 (B1), U12.6 (MOSI)
unnamed: U3.14 (B2), U12.5 (SCK)
unnamed: U3.13 (B3), U12.4 (~CSN)
RTS: Q3.2 (E), R10.1, U9.14 (~RTS)
RX_ESP: D2.1 (K), U6.34 (RXD0/IO3), U9.3 (RXD)
SAMD_A0: U5.4 (A3), U11.3 (PA02)
SAMD_A1: U5.5 (A4), U11.4 (PA03)
SAMD_A3: BZ1.1 (+), U11.6 (PA05)
SAMD_D+: P4.A6 (D+), U11.24 (PA25)
SAMD_D-: P4.A7 (D-), U11.23 (PA24)
SAMD_FLASH_CS: R6.1, U11.11 (PA08)
SAMD_MISO: U5.6 (A5), U11.12 (PA09)
SAMD_MOSI: U5.2 (A1), U11.13 (PA10)
SAMD_RX/A7: J1.1, U11.8 (PA07)
SAMD_SCK: U5.3 (A2), U11.14 (PA11)
SAMD_SCL: R11.2, U6.36 (IO22), U11.18 (PA17)
SAMD_SDA: R1.2, U6.37 (IO23), U11.17 (PA16)
SAMD_TX/A6: J1.2, U11.7 (PA06)
SCK_ESP: U3.3 (A2), U4.4 (SCLK), U6.29 (IO5)
TX_ESP: D1.1 (K), U6.35 (TXD0/IO1), U9.2 (TXD)
USB_D+_ESP: P3.A6 (D+), U9.5 (UD+)
USB__D-_ESP: P3.A7 (D-), U9.6 (UD-)
VBAT: BT1.1 (+), C13.2, C15.1, C16.2, C17.2, Q1.2 (S), R22.1, U8.9 (V_{BAT}), U8.10 (V_{BAT})
VIN_3.3: C21.1, SW8.2 (B), U10.2 (EN), U10.3 (IN)
VS: C1.1, CR1.2, Q1.3 (D), R2.1, SW8.1 (A)

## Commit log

2026-01-27 added files
2026-03-17 added changes
2026-03-17 added needed holes
2026-04-05 changed errors
    new
2026-05-05 chore: reorganize hardware layout and add documentation
2026-05-05 chore: add upload folders for enclosure and FCU top plate
2026-05-05 docs: reorganize README and clarify mechanical upload layout
